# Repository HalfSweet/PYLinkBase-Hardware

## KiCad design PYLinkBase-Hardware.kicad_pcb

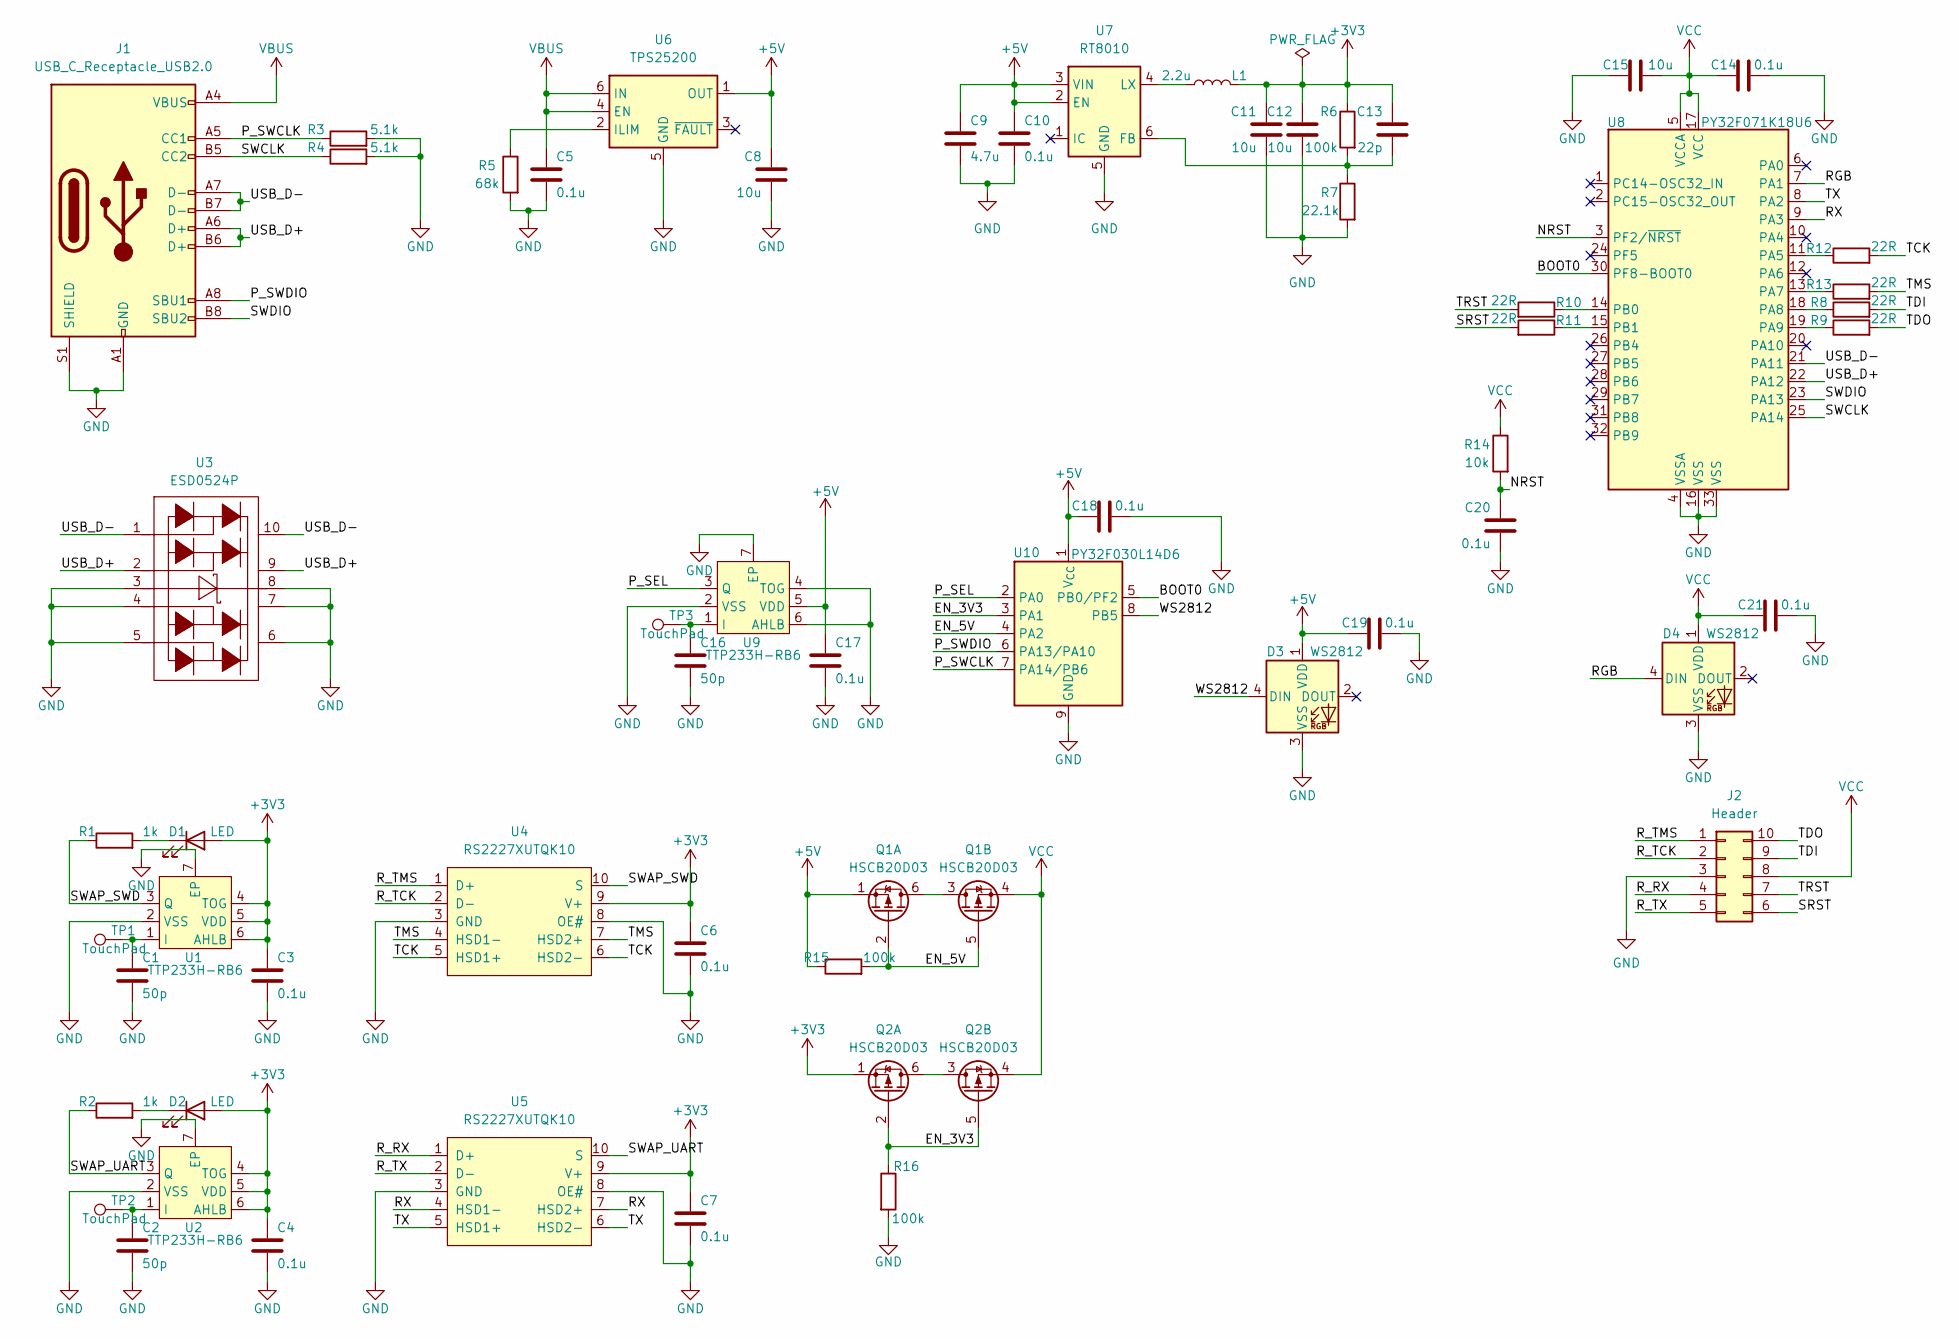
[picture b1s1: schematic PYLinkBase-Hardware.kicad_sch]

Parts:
C1, C2, C16: 50p; C_0402_1005Metric
C3, C4, C5, C6, C7, C10, C14, C17, C18, C19, C20, C21: 0.1u; C_0402_1005Metric
C8, C11, C12, C15: 10u; C_0402_1005Metric
C9: 4.7u; C_0402_1005Metric
C13: 22p; C_0402_1005Metric
D1, D2: LED; LED_0603_1608Metric
D3, D4: WS2812; LED-SMD_4P-L1.0-W1.0-TL_XL-1010RGBC-WS2812B
J1: USB_C_Receptacle_USB2.0; USB_C_Receptacle_G-Switch_GT-USB-7010ASV
J2: Header; Conn_02x05_PinHeader_SMD
L1: 2.2u; L_1008_2520Metric
Q1, Q2: HSCB20D03; DFN-6_L2.0-W2.0-P0.65-BL-EP2
R1, R2: 1k; R_0402_1005Metric
R3, R4: 5.1k; R_0402_1005Metric
R5: 68k; R_0402_1005Metric
R6, R15, R16: 100k; R_0402_1005Metric
R7: 22.1k; R_0402_1005Metric
R8, R9, R10, R11, R12, R13: 22R; R_0402_1005Metric
R14: 10k; R_0402_1005Metric
TP1, TP2, TP3: TouchPad; Touch_SMD_BOX
U1, U2, U9: TTP233H-RB6; DFN-6-1EP_2x2mm_P0.65mm_EP1x1.6mm
U3: ESD0524P; DFN-10_L2.5-W1.0-P0.50-BL-A
U4, U5: RS2227XUTQK10; WQFN-10_L1.8-W1.4-P0.40-BL
U6: TPS25200; DFN-6-1EP_2x2mm_P0.65mm_EP1x1.6mm
U7: RT8010; DFN-6-1EP_2x2mm_P0.65mm_EP1.01x1.7mm
U8: PY32F071K18U6; VQFN-32-1EP_5x5mm_P0.5mm_EP3.5x3.5mm
U10: PY32F030L14D6; DFN-8-1EP_1.5x1.5mm_P0.4mm_EP0.7x1.2mm

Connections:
+3V3: C3.1, C4.1, C6.1, C7.1, C11.1, C12.1, C13.1, D1.2 (A), D2.2 (A), L1.1, Q2.1 (S), R6.1, U1.4 (TOG), U1.5 (VDD), U1.6 (AHLB), U2.4 (TOG), U2.5 (VDD), U2.6 (AHLB), U4.9 (V+), U5.9 (V+)
+5V: C8.1, C9.1, C10.1, C17.1, C18.1, C19.1, D3.1 (VDD), Q1.1 (S), R15.1, U6.1 (OUT), U7.2 (EN), U7.3 (VIN), U9.5 (VDD), U10.1 (V_{CC})
/BOOT0: U8.30 (PF8-BOOT0), U10.5 (PB0/PF2)
/EN_3V3: Q2.2 (G), Q2.5 (G), R16.1, U10.3 (PA1)
/EN_5V: Q1.2 (G), Q1.5 (G), R15.2, U10.4 (PA2)
/NRST: C20.1, R14.2, U8.3 (PF2/~NRST)
/P_SEL: U9.3 (Q), U10.2 (PA0)
/P_SWCLK: J1.A5 (CC1), R3.1, U10.7 (PA14/PB6)
/P_SWDIO: J1.A8 (SBU1), U10.6 (PA13/PA10)
/RGB: D4.4 (DIN), U8.7 (PA1)
/RX: U5.4 (HSD1-), U5.7 (HSD2+), U8.9 (PA3)
/R_RX: J2.4, U5.1 (D+)
/R_TCK: J2.2, U4.2 (D-)
/R_TMS: J2.1, U4.1 (D+)
/R_TX: J2.5, U5.2 (D-)
/SRST: J2.6, R11.2
/SWAP_SWD: R1.1, U1.3 (Q), U4.10 (S)
/SWAP_UART: R2.1, U2.3 (Q), U5.10 (S)
/SWCLK: J1.B5 (CC2), R4.1, U8.25 (PA14)
/SWDIO: J1.B8 (SBU2), U8.23 (PA13)
/TCK: R12.2, U4.5 (HSD1+), U4.6 (HSD2-)
/TDI: J2.9, R8.2
/TDO: J2.10, R9.2
/TMS: R13.2, U4.4 (HSD1-), U4.7 (HSD2+)
/TRST: J2.7, R10.2
/TX: U5.5 (HSD1+), U5.6 (HSD2-), U8.8 (PA2)
/USB_D+: J1.A6 (D+), J1.B6 (D+), U3.2, U3.9, U8.22 (PA12)
/USB_D-: J1.A7 (D-), J1.B7 (D-), U3.1, U3.10, U8.21 (PA11)
/WS2812: D3.4 (DIN), U10.8 (PB5)
GND: C1.2, C2.2, C3.2, C4.2, C5.2, C6.2, C7.2, C8.2, C9.2, C10.2, C11.2, C12.2, C14.2, C15.1, C16.2, C17.2, C18.2, C19.2, C20.2, C21.2, D3.3 (VSS), D4.3 (VSS), J1.A1 (GND), J1.A12 (GND), J1.B1 (GND), J1.B12 (GND), J1.S1 (SHIELD), J2.3, R3.2, R4.2, R5.2, R7.2, R16.2, U1.2 (VSS), U1.7 (EP), U2.2 (VSS), U2.7 (EP), U3.3, U3.4, U3.5, U3.6, U3.7, U3.8, U4.3 (GND), U4.8 (OE#), U5.3 (GND), U5.8 (OE#), U6.5 (GND), U6.7 (GND), U7.5 (GND), U7.7 (GND), U8.4 (VSSA), U8.16 (VSS), U8.33 (VSS), U9.2 (VSS), U9.4 (TOG), U9.6 (AHLB), U9.7 (EP), U10.9 (GND)
unnamed: D1.1 (K), R1.2
unnamed: D2.1 (K), R2.2
unnamed: Q1.3 (D), Q1.6 (D)
unnamed: Q2.3 (D), Q2.6 (D)
unnamed: C1.1, TP1.1, U1.1 (I)
unnamed: C2.1, TP2.1, U2.1 (I)
unnamed: R5.1, U6.2 (ILIM)
unnamed: C13.2, R6.2, R7.1, U7.6 (FB)
unnamed: L1.2, U7.4 (LX)
unnamed: R12.1, U8.11 (PA5)
unnamed: R13.1, U8.13 (PA7)
unnamed: R8.1, U8.18 (PA8)
unnamed: R9.1, U8.19 (PA9)
unnamed: R10.1, U8.14 (PB0)
unnamed: R11.1, U8.15 (PB1)
unnamed: C16.1, TP3.1, U9.1 (I)
VBUS: C5.1, J1.A4 (VBUS), J1.A9 (VBUS), J1.B4 (VBUS), J1.B9 (VBUS), U6.4 (EN), U6.6 (IN)
VCC: C14.1, C15.2, C21.1, D4.1 (VDD), J2.8, Q1.4 (S), Q2.4 (S), R14.1, U8.5 (VCCA), U8.17 (VCC)

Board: 2 copper layers, 59 parts (0 on the bottom side), 47 nets, no tracks yet.

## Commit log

2024-07-26 add: 添加初步的原理图和PCB
